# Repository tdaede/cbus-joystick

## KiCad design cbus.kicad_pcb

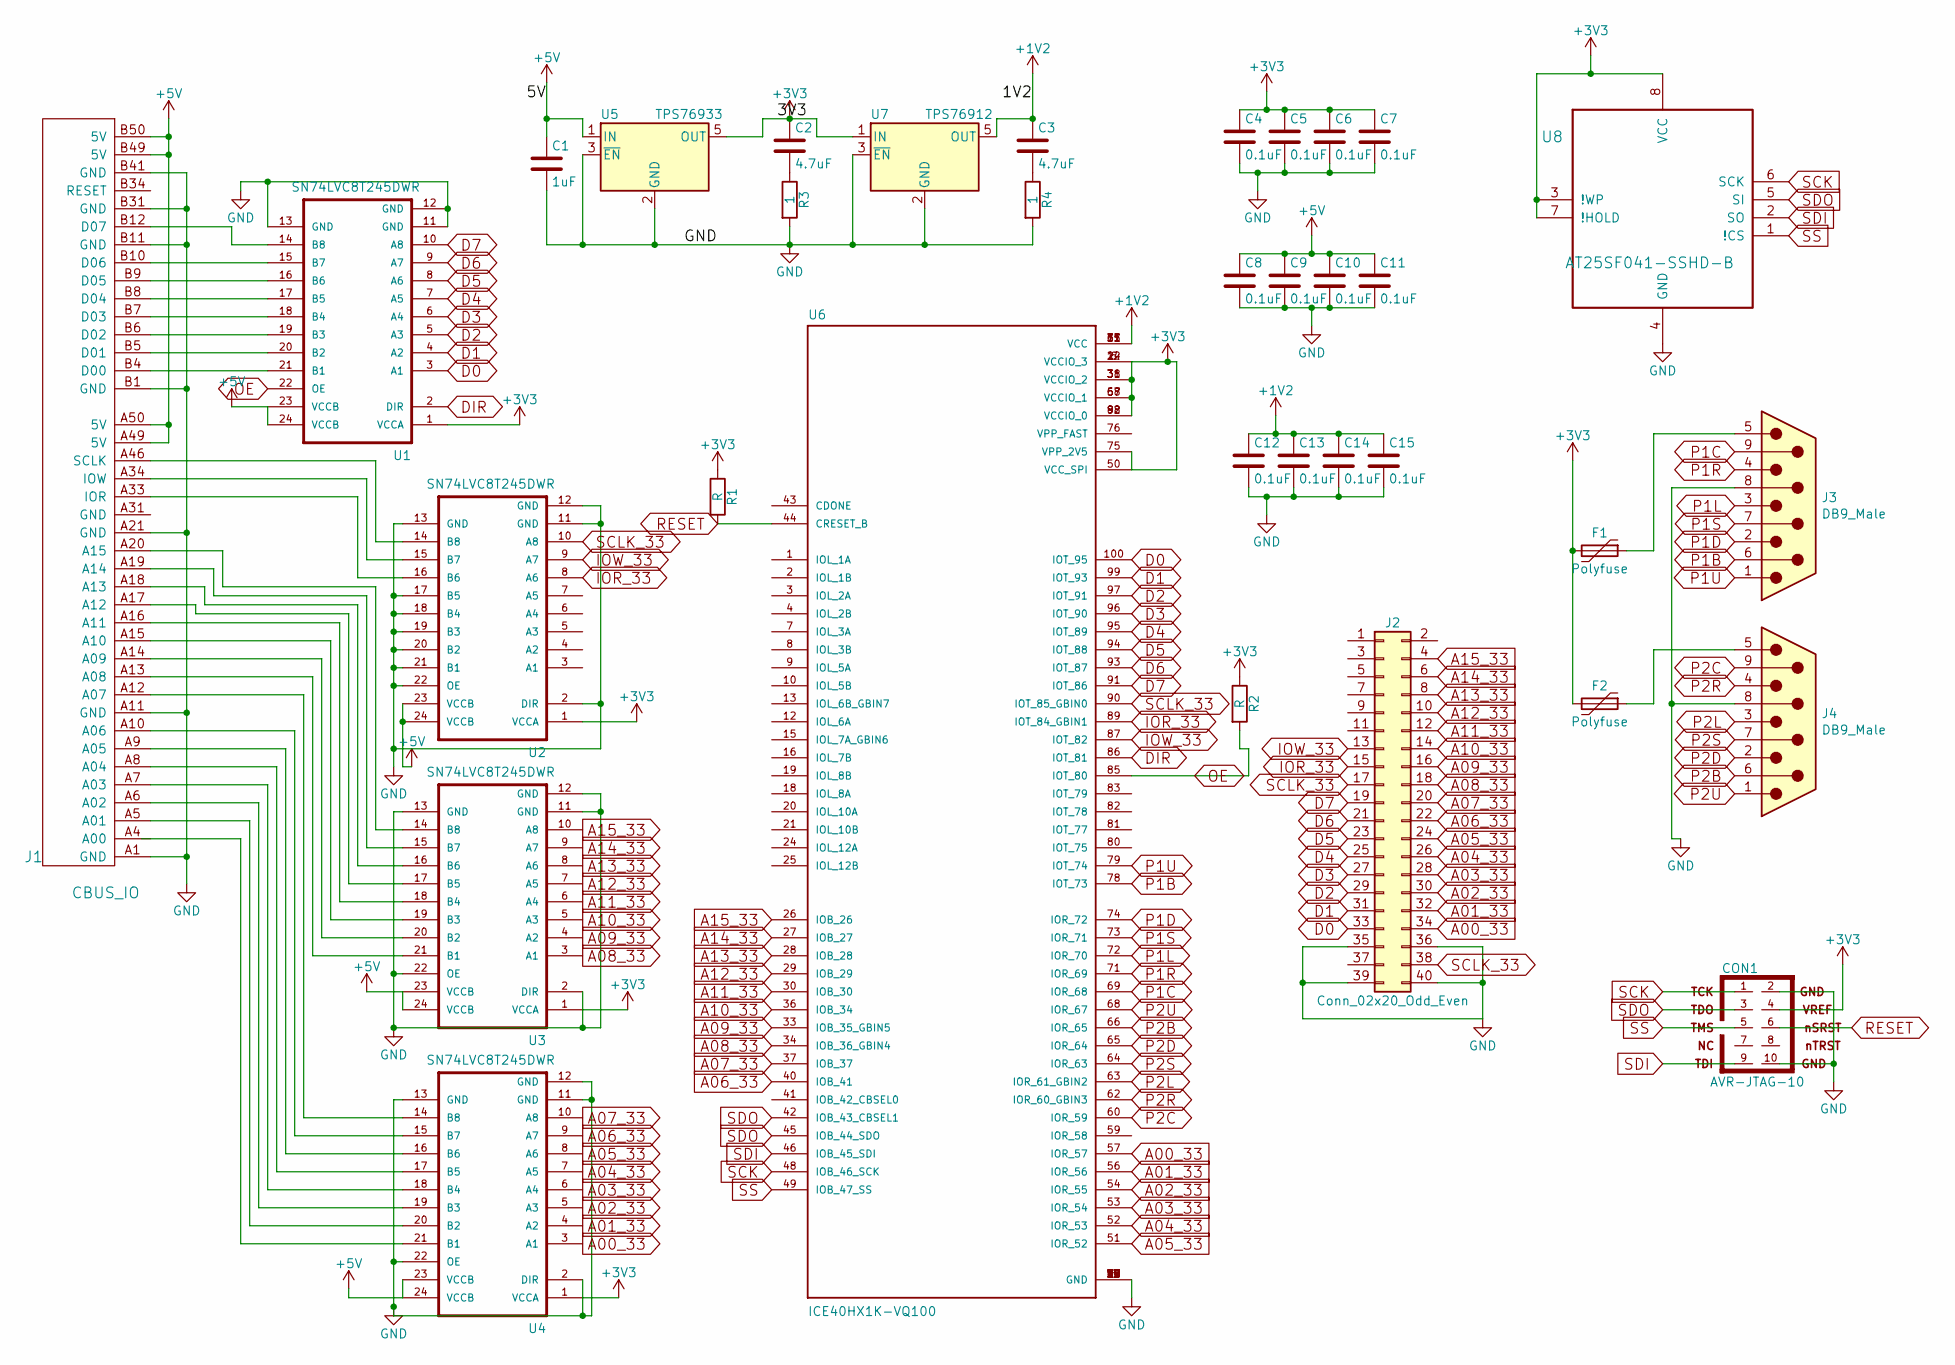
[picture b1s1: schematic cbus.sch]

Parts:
C1: 1uF; C_0805_HandSoldering
C2, C3: 4.7uF; C_0805_HandSoldering
C4, C5, C6, C7, C8, C9, C10, C11, C12, C13, C14, C15: 0.1uF; C_0805_HandSoldering
CON1: AVR-JTAG-10; IDC-Header_2x05_Pitch2.54mm_Straight
F1, F2: Polyfuse; R_0805_HandSoldering
J1: CBUS_IO; cbus_io
J2: Conn_02x20_Odd_Even; IDC-Header_2x20_Pitch2.54mm_Straight
J3, J4: DB9_Male; DSUB-9_Male_Horizontal_P2.77x2.84mm_EdgePinOffset4.94mm_Hou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
R1, R2: R; R_0805_HandSoldering
R3, R4: 1; R_0805_HandSoldering
U1, U2, U3, U4: SN74LVC8T245DWR; SOIC127P1030X265-24N
U5: TPS76933; SOT-23-5
U6: ICE40HX1K-VQ100; QFP50P1600X1600X120-100N
U7: TPS76912; SOT-23-5
U8: AT25SF041-SSHD-B; SOIC-8_3.9x4.9mm_Pitch1.27mm

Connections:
+1V2: C3.1, C12.1, C13.1, C14.1, C15.1, U6.11 (VCC), U6.35 (VCC), U6.61 (VCC), U6.77 (VCC), U7.5 (OUT)
+3V3: C2.1, C4.1, C5.1, C6.1, C7.1, CON1.4, F1.2, F2.2, R1.1, R2.1, U1.1 (VCCA), U2.1 (VCCA), U3.1 (VCCA), U4.1 (VCCA), U5.5 (OUT), U6.6 (VCCIO_3), U6.14 (VCCIO_3), U6.22 (VCCIO_3), U6.31 (VCCIO_2), U6.38 (VCCIO_2), U6.50 (VCC_SPI), U6.58 (VCCIO_1), U6.67 (VCCIO_1), U6.75 (VPP_2V5), U6.88 (VCCIO_0), U6.92 (VCCIO_0), U7.1 (IN), U8.3 (!WP), U8.7 (!HOLD), U8.8 (VCC)
+5V: C1.1, C8.1, C9.1, C10.1, C11.1, J1.A49 (5V), J1.A50 (5V), J1.B49 (5V), J1.B50 (5V), U1.23 (VCCB), U1.24 (VCCB), U2.23 (VCCB), U2.24 (VCCB), U3.23 (VCCB), U3.24 (VCCB), U4.23 (VCCB), U4.24 (VCCB), U5.1 (IN)
A00_33: J2.34, U4.3 (A1), U6.57 (IOR_57)
A01_33: J2.32, U4.4 (A2), U6.56 (IOR_56)
A02_33: J2.30, U4.5 (A3), U6.54 (IOR_55)
A03_33: J2.28, U4.6 (A4), U6.53 (IOR_54)
A04_33: J2.26, U4.7 (A5), U6.52 (IOR_53)
A05_33: J2.24, U4.8 (A6), U6.51 (IOR_52)
A06_33: J2.22, U4.9 (A7), U6.40 (IOB_41)
A07_33: J2.20, U4.10 (A8), U6.37 (IOB_37)
A08_33: J2.18, U3.3 (A1), U6.34 (IOB_36_GBIN4)
A09_33: J2.16, U3.4 (A2), U6.33 (IOB_35_GBIN5)
A10_33: J2.14, U3.5 (A3), U6.36 (IOB_34)
A11_33: J2.12, U3.6 (A4), U6.30 (IOB_30)
A12_33: J2.10, U3.7 (A5), U6.29 (IOB_29)
A13_33: J2.8, U3.8 (A6), U6.28 (IOB_28)
A14_33: J2.6, U3.9 (A7), U6.27 (IOB_27)
A15_33: J2.4, U3.10 (A8), U6.26 (IOB_26)
D0: J2.33, U1.3 (A1), U6.100 (IOT_95)
D1: J2.31, U1.4 (A2), U6.99 (IOT_93)
D2: J2.29, U1.5 (A3), U6.97 (IOT_91)
D3: J2.27, U1.6 (A4), U6.96 (IOT_90)
D4: J2.25, U1.7 (A5), U6.95 (IOT_89)
D5: J2.23, U1.8 (A6), U6.94 (IOT_88)
D6: J2.21, U1.9 (A7), U6.93 (IOT_87)
D7: J2.19, U1.10 (A8), U6.91 (IOT_86)
DIR: U1.2 (DIR), U6.86 (IOT_81)
GND: C1.2, C4.2, C5.2, C6.2, C7.2, C8.2, C9.2, C10.2, C11.2, C12.2, C13.2, C14.2, C15.2, CON1.2, CON1.10, J1.A1 (GND), J1.A11 (GND), J1.A21 (GND), J1.B1 (GND), J1.B11 (GND), J1.B31 (GND), J1.B41 (GND), J2.35, J2.36, J2.39, J2.40, J3.8, J4.8, R3.2, R4.2, U1.11 (GND), U1.12 (GND), U1.13 (GND), U2.2 (DIR), U2.11 (GND), U2.12 (GND), U2.13 (GND), U2.17 (B5), U2.18 (B4), U2.19 (B3), U2.20 (B2), U2.21 (B1), U2.22 (OE), U3.2 (DIR), U3.11 (GND), U3.12 (GND), U3.13 (GND), U3.22 (OE), U4.2 (DIR), U4.11 (GND), U4.12 (GND), U4.13 (GND), U4.22 (OE), U5.2 (GND), U5.3 (~EN~), U6.5 (GND), U6.17 (GND), U6.23 (GND), U6.32 (GND), U6.39 (GND), U6.47 (GND), U6.55 (GND), U6.70 (GND), U6.84 (GND), U6.98 (GND), U7.2 (GND), U7.3 (~EN~), U8.4 (GND)
IOR_33: J2.15, U2.8 (A6), U6.89 (IOT_84_GBIN1)
IOW_33: J2.13, U2.9 (A7), U6.87 (IOT_82)
unnamed: C2.2, R3.1
unnamed: C3.2, R4.1
unnamed: F1.1, J3.5
unnamed: F2.1, J4.5
unnamed: J1.A5 (A01), U4.20 (B2)
unnamed: J1.A6 (A02), U4.19 (B3)
unnamed: J1.A7 (A03), U4.18 (B4)
unnamed: J1.A8 (A04), U4.17 (B5)
unnamed: J1.A9 (A05), U4.16 (B6)
unnamed: J1.A10 (A06), U4.15 (B7)
unnamed: J1.A12 (A07), U4.14 (B8)
unnamed: J1.A13 (A08), U3.21 (B1)
unnamed: J1.A14 (A09), U3.20 (B2)
unnamed: J1.A15 (A10), U3.19 (B3)
unnamed: J1.A16 (A11), U3.18 (B4)
unnamed: J1.A17 (A12), U3.17 (B5)
unnamed: J1.A18 (A13), U3.16 (B6)
unnamed: J1.A19 (A14), U3.15 (B7)
unnamed: J1.A20 (A15), U3.14 (B8)
unnamed: J1.A33 (IOR), U2.16 (B6)
unnamed: J1.A34 (IOW), U2.15 (B7)
unnamed: J1.A46 (SCLK), U2.14 (B8)
unnamed: J1.B4 (D00), U1.21 (B1)
unnamed: J1.B5 (D01), U1.20 (B2)
unnamed: J1.B6 (D02), U1.19 (B3)
unnamed: J1.B7 (D03), U1.18 (B4)
unnamed: J1.B8 (D04), U1.17 (B5)
unnamed: J1.B9 (D05), U1.16 (B6)
unnamed: J1.B10 (D06), U1.15 (B7)
unnamed: J1.B12 (D07), U1.14 (B8)
OE: R2.2, U1.22 (OE), U6.85 (IOT_80)
P1B: J3.6, U6.78 (IOT_73)
P1C: J3.9, U6.69 (IOR_68)
P1D: J3.2, U6.74 (IOR_72)
P1L: J3.3, U6.72 (IOR_70)
P1R: J3.4, U6.71 (IOR_69)
P1S: J3.7, U6.73 (IOR_71)
P1U: J3.1, U6.79 (IOT_74)
P2B: J4.6, U6.66 (IOR_65)
P2C: J4.9, U6.60 (IOR_59)
P2D: J4.2, U6.65 (IOR_64)
P2L: J4.3, U6.63 (IOR_61_GBIN2)
P2R: J4.4, U6.62 (IOR_60_GBIN3)
P2S: J4.7, U6.64 (IOR_63)
P2U: J4.1, U6.68 (IOR_67)
RESET: CON1.6, R1.2, U6.44 (CRESET_B)
SCK: CON1.1, U6.48 (IOB_46_SCK), U8.6 (SCK)
SCLK_33: J2.17, J2.38, U2.10 (A8), U6.90 (IOT_85_GBIN0)
SDI: CON1.9, U6.46 (IOB_45_SDI), U8.2 (SO)
SDO: CON1.3, U6.42 (IOB_43_CBSEL1), U6.45 (IOB_44_SDO), U8.5 (SI)
SS: CON1.5, U6.49 (IOB_47_SS), U8.1 (!CS)

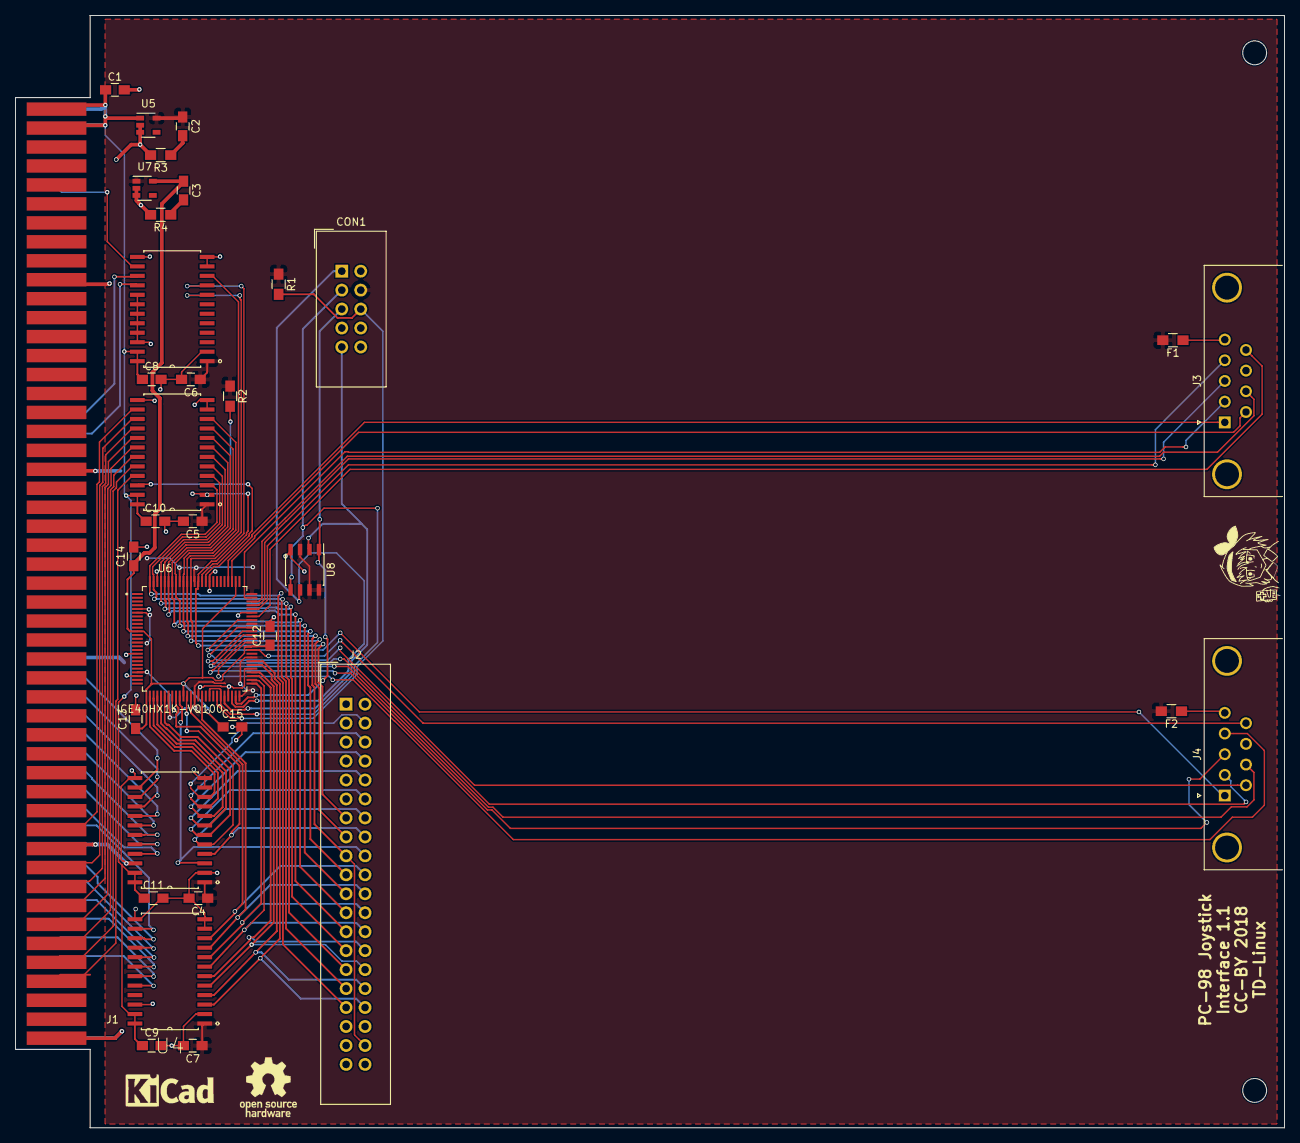
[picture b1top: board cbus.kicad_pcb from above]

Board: 2 copper layers, 170.0 x 149.0 mm, 35 parts (0 on the bottom side), 82 nets.

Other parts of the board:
svg2mod: G***; alice2

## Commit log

2018-08-19 Finish routing
2018-08-29 Add some missed files and LICENSE
2018-09-04 Fix connector spacing
2018-09-05 Longboi
2018-09-05 set PCB page size to letter
2018-09-07 Routing for v1.1
2018-09-10 Add 3D models
2018-09-14 Add fpga source code.
2018-09-14 make LED blink
2018-09-27 Make p1 work
2018-09-27 fix p1 s signal
2018-09-28 Add two-player support
2018-09-28 Remove counter
2018-09-28 use pullup for select line

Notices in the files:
cbus.kicad_pcb:
CC-BY 2018
